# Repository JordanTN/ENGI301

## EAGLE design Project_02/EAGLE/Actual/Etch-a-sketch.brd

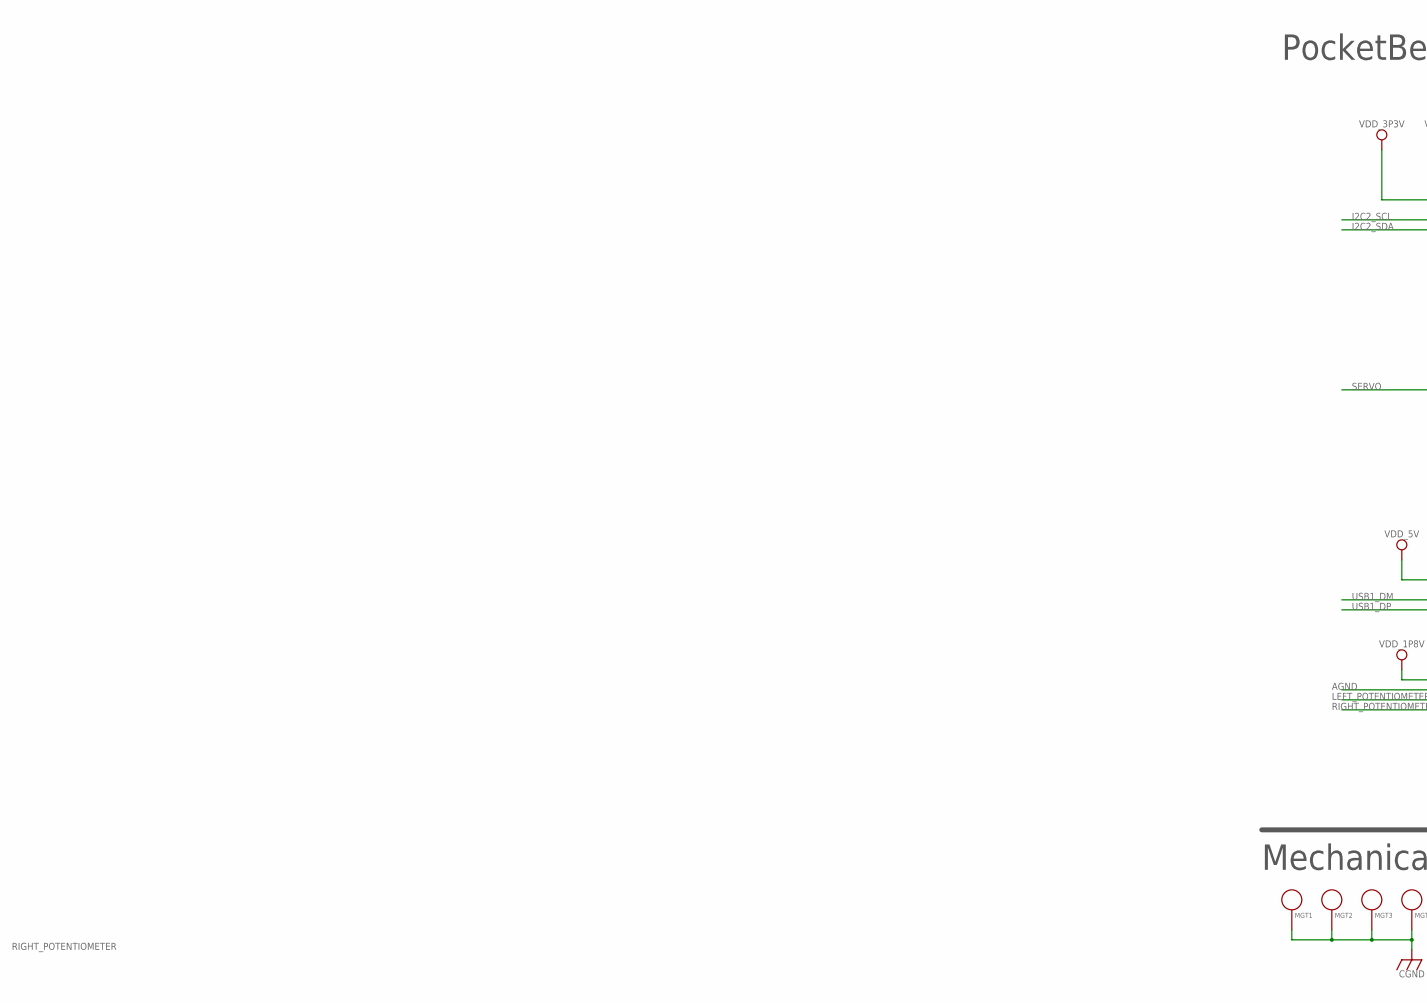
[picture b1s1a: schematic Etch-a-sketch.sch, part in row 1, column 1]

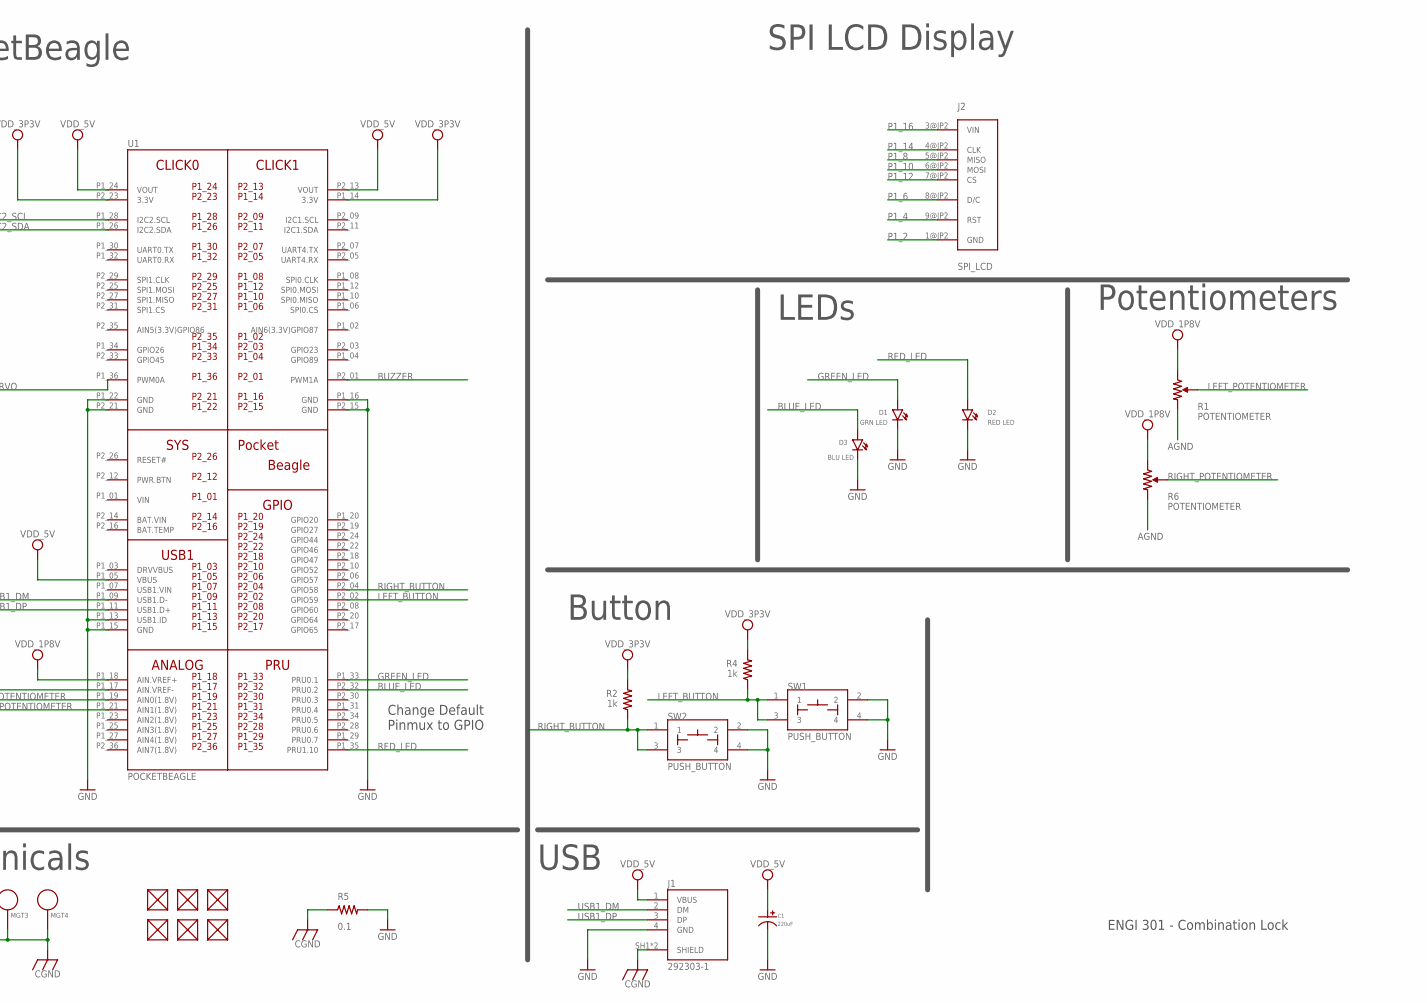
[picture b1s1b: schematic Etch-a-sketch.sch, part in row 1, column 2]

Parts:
C1: 220uF; CP10MM
D1, D3: GRN LED; EIA-STD
D2: RED LED; EIA-STD
FUD1, FUD2, FUD3, FUD4, FUD5, FUD6: FIDUCIAL; FIDUCIAL_40MIL
J1: 292303-1; TE_292303-1
J2: SPI_LCD; TFT_LCD_PCB
MGT1, MGT2, MGT3, MGT4: MOUNTING_HOLE
R1, R6: POTENTIOMETER; POT-PO90S
R2, R4: 1k; R0603
R5: 0.1; R0805
SW1, SW2: PUSH_BUTTON; BUTTON_12.5MM
U1: POCKETBEAGLE

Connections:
AGND: R1.CW, R6.CW, U1.P1_17 (AIN.VREF-)
AGND1: U1.P1_21 (AIN1(1.8V))
BAT.VIN: U1.P2_14 (BAT.VIN)
BUTTON1: U1.P2_04 (GPIO58)
BUZZER: U1.P2_01 (PWM1A)
CGND: J1.SH1 (SHIELD), J1.SH2 (SHIELD), MGT1.P$1, MGT2.P$1, MGT3.P$1, MGT4.P$1, R5.1
GND: C1.P$2, D1.CATHODE, D2.CATHODE, D3.CATHODE, J1.4 (GND), R5.2, SW1.2, SW1.4, SW2.2, SW2.4, U1.P1_13 (USB1.ID), U1.P1_15 (GND), U1.P1_16 (GND), U1.P1_22 (GND), U1.P2_15 (GND), U1.P2_21 (GND)
GREEN_LED: D1.ANODE, D3.ANODE, U1.P1_33 (PRU0.1)
GREEN_LED1: U1.P2_32 (PRU0.2)
I2C2_SCL: U1.P1_28 (I2C2.SCL)
I2C2_SDA: U1.P1_26 (I2C2.SDA)
LEFT_BUTTON: R2.1, R4.1, SW1.1, SW1.3, SW2.1, SW2.3, U1.P2_02 (GPIO59)
LEFT_POTENTIOMETER: R1.S, R6.S, U1.P1_19 (AIN0(1.8V))
RED_LED: D2.ANODE, U1.P1_35 (PRU1.10)
SERVO: U1.P1_36 (PWM0A)
USB1_DM: J1.2 (DM), U1.P1_09 (USB1.D-)
USB1_DP: J1.3 (DP), U1.P1_11 (USB1.D+)
VDD_1P8V: R1.CCW, R6.CCW, U1.P1_18 (AIN.VREF+)
VDD_3P3V: R2.2, R4.2, U1.P1_14 (3.3V), U1.P2_23 (3.3V)
VDD_5V: C1.P$1, J1.1 (VBUS), U1.P1_05 (VBUS), U1.P1_24 (VOUT), U1.P2_13 (VOUT)
VIN: U1.P1_01 (VIN)

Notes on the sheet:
LEDs
Potentiometers
SPI LCD Display
Button
PocketBeagle
ENGI 301 - Combination Lock
Mechanicals
Change Default Pinmux to GPIO
USB
RIGHT_BUTTON
RIGHT_POTENTIOMETER
BLUE_LED
BLU LED
P1_16
P1_14
P1_8
P1_10
P1_12
P1_6
P1_4
P1_2

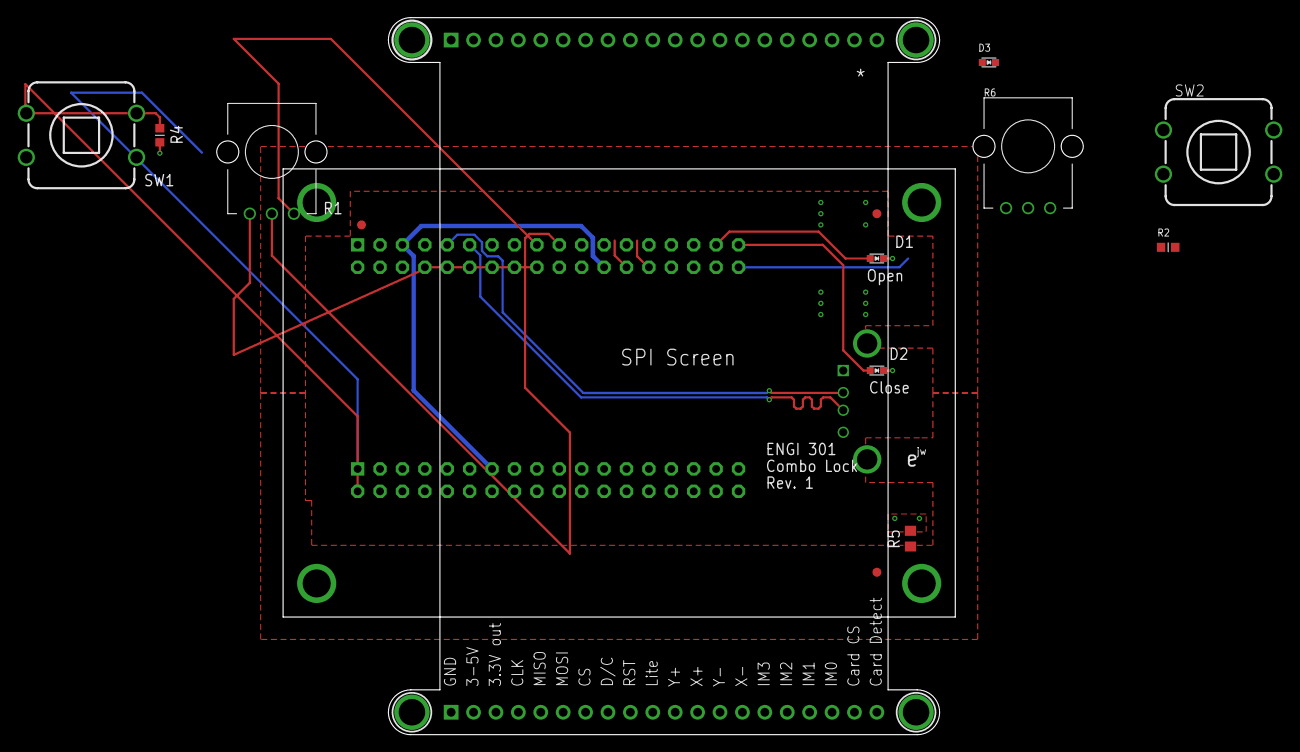
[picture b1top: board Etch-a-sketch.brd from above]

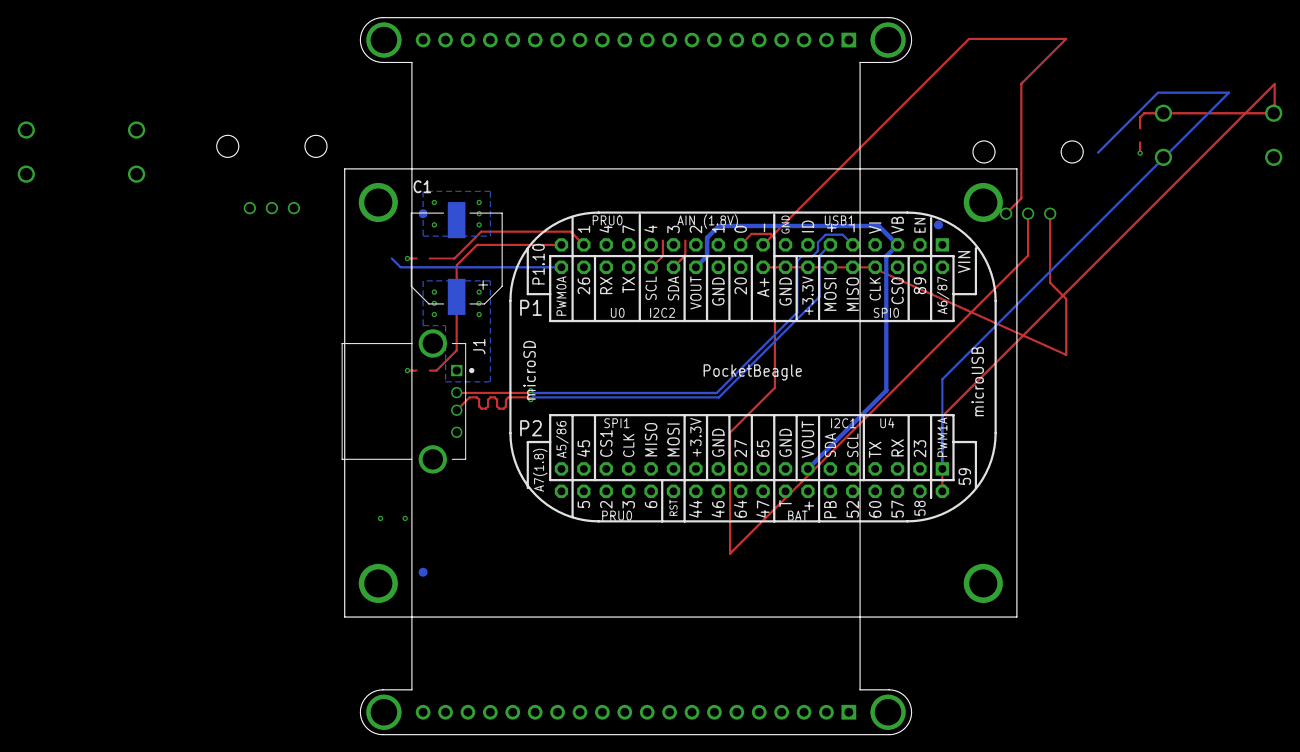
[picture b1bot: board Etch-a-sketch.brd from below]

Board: 4 copper layers, 24 parts (6 on the bottom side), 12 nets.

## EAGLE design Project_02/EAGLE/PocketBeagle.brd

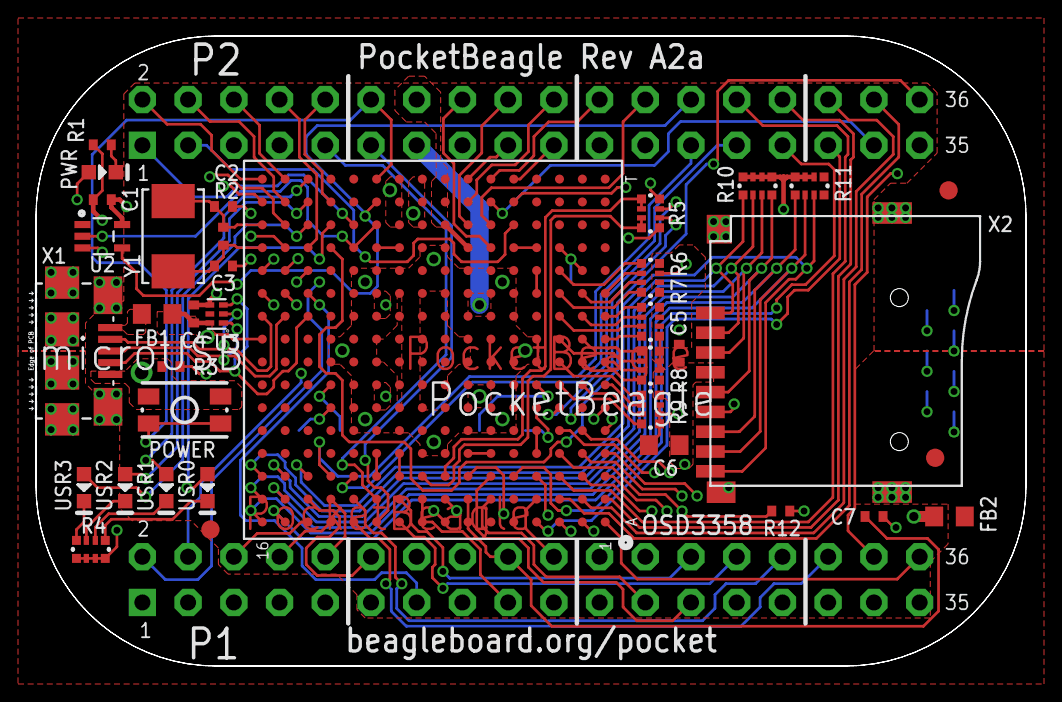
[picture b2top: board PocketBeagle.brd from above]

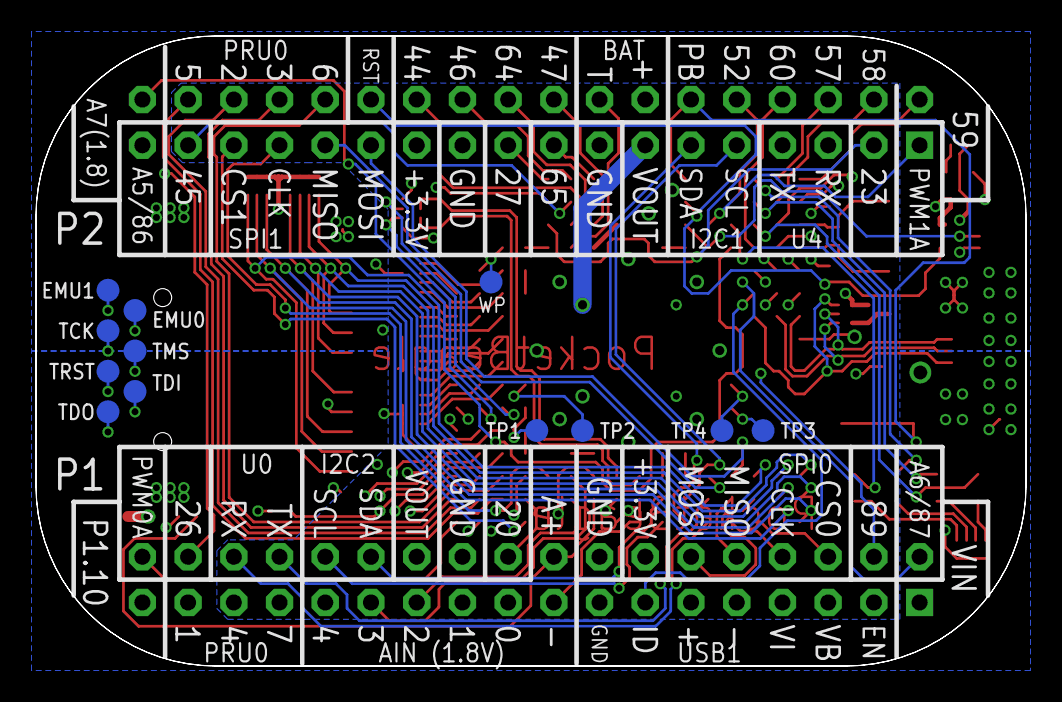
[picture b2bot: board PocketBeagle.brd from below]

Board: 4 copper layers, 55.0 x 35.0 mm, 50 parts (12 on the bottom side), 133 nets.

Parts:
C1, C5, C7: 0.1uF, 6.3V; 0402
C2, C3: 18pF, 50V; 0402
C4: .1uF, 6.3V; 0402
C6: 10uF, 10V; 0603
EMU0, EMU1: PTR1B1,27; B1,27
FB1, FB2: 0603
FUD1, FUD2, FUD3: FIDUCIAL; FIDUCIAL_40MIL
P1, P2: TH-2X18-(35MIL-DIA)-W/O-SILK
POWER: MINI_PUSHBUTTON
PWR: LTST-C191TBKT; 0603-LED
R1: 1k; 0402
R2: 1M, 1%; 0402
R3, R12: 10k; 0402
R4: 1k; RN0804
R5, R10, R11: 10k; RN0804
R6, R7, R8, R9: 100k; RN0804
TCK: PTR1B1,27; B1,27
TDI: PTR1B1,27; B1,27
TDO: PTR1B1,27; B1,27
TMS: PTR1B1,27; B1,27
TP1, TP2, TP3, TP4: PTR1B1,27; B1,27
TRST: PTR1B1,27; B1,27
U1: OSD3358-512M-BSM; OSD335X-BGA-256
U2: SN74LVC1G07DCK; SC70(TI-DCK)
U3: TPD4S012DRY; SON-6(TI)-DRY
USR0, USR1, USR2, USR3: LTST-C191TBKT; 0603-LED
WP: PTR1B1,27; B1,27
X1: 10118192-0001LF; 10118192-0001LF(MICRO-USB-B-AMPHENOL-FCI)
X2: MICROSD
Y1: 24 MHz; CRYSTAL_5X3.2MM

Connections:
3.3V: C5.1, C6.1, P1.14, P2.23, R6.7, R8.5, R9.4, R10.5, R10.6, R10.7, R10.8, R11.2, R11.3, R11.4, U1.F6, U1.F7, U1.G6, U1.G7, X2.4
(U1.A15)MMC0.D1: R11.6, U1.A15, X2.8
(U1.A16)MMC0.D0: R11.5, U1.A16, X2.7
(U1.B15)MMC0.CLK: R10.4, U1.B15, X2.5
(U1.B16)MMC0.CMD: R10.3, U1.B16, X2.3
(U1.C8)AIN5~1.8V: R5.1, R5.2, U1.C8
(U1.C9)AIN6~1.8V: R5.3, R5.4, U1.C9
(U1.C14)MMC0.CD: R11.7, U1.C14, X2.9
(U1.C15)MMC0.D3: R10.2, U1.C15, X2.2
(U1.C16)MMC0.D2: R10.1, U1.C16, X2.1
(U1.G1)LCD.D2.B5: R9.6, U1.G1
(U1.G2)LCD.D1.B4: R9.7, U1.G2
(U1.G3)LCD.D0.B3: R9.8, U1.G3
(U1.H1)LCD.D5.G2: R8.3, U1.H1
(U1.H2)LCD.D4.B7: R8.4, U1.H2
(U1.H3)LCD.D3.B6: R9.5, U1.H3
(U1.J1)LCD.D8.G5: R7.4, U1.J1
(U1.J2)LCD.D7.G4: R8.1, U1.J2
(U1.J3)LCD.D6.G3: R8.2, U1.J3
(U1.K1)LCD.D11.R3: R7.1, U1.K1
(U1.K2)LCD.D10.G7: R7.2, U1.K2
(U1.K3)LCD.D9.G6: R7.3, U1.K3
(U1.K14)USBC.ID: U1.K14, U3.3, X1.ID
(U1.K15)USBC.D+: U1.K15, U3.1, X1.D+
(U1.K16)USBC.D-: U1.K16, U3.2, X1.D-
(U1.L1)LCD.D14.R6: R6.2, U1.L1
(U1.L2)LCD.D13.R5: R6.3, U1.L2
(U1.L3)LCD.D12.R4: R6.4, U1.L3
(U1.M2)EEPROM.WP: U1.M2, U1.N3, WP.TP
(U1.M3)LCD.D15.R7: R6.1, U1.M3
(U1.P13)USR0: U1.P13, USR0.A
(U1.P14)USR3: U1.P14, USR3.A
(U1.R14)USR2: U1.R14, USR2.A
(U1.T14)USR1: U1.T14, USR1.A
AIN0(1.8V): P1.19, U1.A8
AIN1(1.8V): P1.21, U1.B8
AIN2(1.8V): P1.23, U1.B6
AIN3(1.8V): P1.25, U1.C6
AIN4(1.8V): P1.27, U1.C7
AIN5(3.3V): P2.35, R5.7, U1.F3
AIN6/GPIO87: P1.2, R5.6, U1.F2
AIN7(1.8V): P2.36, U1.N13
AIN.VREF+: C7.1, P1.18, U1.A7, U1.B7
AIN.VREF-: C7.2, P1.17, U1.A9, U1.B9
BAT.TEMP: P2.16, U1.N6
BAT.VIN: P2.14, U1.N7, U1.P8, U1.R8, U1.T8
CGND: FB2.1, X1.CGND1, X1.CGND2, X1.CGND3, X1.CGND4, X1.CGND5, X1.CGND6, X2.G1, X2.G2, X2.G3, X2.G4
GND: C1.2, C4.2, C5.2, C6.2, FB2.2, P1.15, P1.16, P1.22, P2.15, P2.21, POWER.1, POWER.2, R1.1, R3.1, R4.5, R4.6, R4.7, R4.8, R5.5, R5.8, R6.5, R6.6, R6.8, R7.5, R7.6, R7.7, R7.8, R8.6, R8.7, R8.8, R9.1, R9.2, R9.3, R12.1, U1.D8, U1.D9, U1.E5, U1.E6, U1.E7, U1.E8, U1.E9, U1.E10, U1.E11, U1.E12, U1.F5, U1.F12, U1.G5, U1.G12, U1.H4, U1.H5, U1.H12, U1.H13, U1.J4, U1.J5, U1.J12, U1.J13, U1.K5, U1.K12, U1.L5, U1.L12, U1.M5, U1.M6, U1.M7, U1.M8, U1.M9, U1.M10, U1.M11, U1.M12, U1.N8, U1.N9, U2.3, U3.4, X1.GND, X2.6
GPIO20: P1.20, U1.B4
GPIO23: P2.3, U1.P5
GPIO26: P1.34, U1.R5
GPIO27: P2.19, U1.T5
GPIO44: P2.24, U1.P6
GPIO45: P2.33, U1.R6
GPIO46: P2.22, U1.T6
GPIO47: P2.18, U1.P7
GPIO52: P2.10, U1.R13
GPIO57: P2.6, U1.T15
GPIO58: P2.4, U1.R15
GPIO59: P2.2, U1.T16
GPIO60: P2.8, U1.N14
GPIO64: P2.20, U1.R7
GPIO65: P2.17, U1.T7
GPIO89: P1.4, U1.E1
I2C1.SCL: P2.9, U1.B11
I2C1.SDA: P2.11, U1.A11
I2C2.SCL: P1.28, U1.A10
I2C2.SDA: P1.26, U1.B10
JTAG_EMU0: EMU0.TP, U1.E2
JTAG_EMU1: EMU1.TP, U1.E3
JTAG_TCK: TCK.TP, U1.D1
JTAG_TDI: TDI.TP, U1.C1
JTAG_TDO: TDO.TP, U1.C2
JTAG_TMS: TMS.TP, U1.D2
JTAG_TRST#: R12.2, TRST.TP, U1.D3
unnamed: R4.3, USR2.K
unnamed: R4.4, USR3.K
unnamed: PWR.K, R1.2
unnamed: R4.2, USR1.K
unnamed: R4.1, USR0.K
unnamed: TP1.TP, U1.F4
unnamed: TP2.TP, U1.G4
unnamed: TP3.TP, U1.F13
unnamed: TP4.TP, U1.G13
unnamed: U1.D6, U1.D7
unnamed: R3.2, U1.M16
unnamed: U1.N4, U1.N5
unnamed: U1.L4, U1.M4
unnamed: U1.D4, U1.E4
unnamed: U1.N10, U1.N11
unnamed: U1.C11, U1.D11
unnamed: U1.C10, U1.D10
OSC.GND: C2.1, C3.1, U1.N15
OSC.IN: C2.2, R2.2, U1.P16, Y1.2
OSC.OUT: C3.2, R2.1, U1.N16, Y1.1
PMIC_PGOOD: U1.N12, U1.P11, U2.2
PRU0.1: P1.33, U1.A2
PRU0.2: P2.32, U1.B2
PRU0.3: P2.30, U1.B1
PRU0.4: P1.31, U1.A3
PRU0.5: P2.34, U1.B3
PRU0.6: P2.28, U1.C3
PRU0.7: P1.29, U1.C4
PRU1.10: P1.35, U1.F1
PWM0A: P1.36, U1.A1
PWM1A: P2.1, U1.P12
PWR.BTN: P2.12, POWER.3, POWER.4, U1.T11
RESET#: P2.26, U1.R11, U2.4
SPI0.CLK: P1.8, U1.A13
SPI0.CS: P1.6, U1.A14
SPI0.MISO: P1.10, U1.B13
SPI0.MOSI: P1.12, U1.B14
SPI1.CLK: P2.29, U1.C5
SPI1.CS: P2.31, U1.A4
SPI1.MISO: P2.27, U1.C12
SPI1.MOSI: P2.25, U1.C13
UART0.RX: P1.32, U1.A12
UART0.TX: P1.30, U1.B12
UART4.RX: P2.5, U1.P15
UART4.TX: P2.7, U1.R16
USB1.D+: P1.11, U1.L15
USB1.D-: P1.9, U1.L16
USB1.DRVVBUS: P1.3, U1.M14
USB1.ID: P1.13, U1.L14
USB1.VBUS: P1.5, U1.M15
VBUS.RAW: FB1.1, X1.VBUS
VDD_1V8: U1.F10, U1.G10, U1.H10, U1.H11, U1.J10, U1.J11, U1.K10, U1.L10
VDD_3V3A: U1.F8, U1.F9, U1.G8, U1.G9, U1.H7, U1.H8, U1.H9, U1.J7, U1.J8, U1.J9, U1.K8, U1.K9, U1.L8, U1.L9
VDD_3V3AUX: PWR.A, U1.F11, U1.G11
VDD_RTC: C1.1, U1.K11, U1.L11, U2.5
VIN: P1.1, U1.P10, U1.R10, U1.T10
VIN.USB: C4.1, FB1.2, P1.7, U1.J16, U1.P9, U1.R9, U1.T9, U3.6
VOUT: P1.24, P2.13, U1.K6, U1.K7, U1.L6, U1.L7

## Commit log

2022-09-19 hw4 question1 added
2022-09-19 blink USR3 at 5 Hz
2022-10-04 Create proposal
2022-12-03 1st update
2022-12-05 README
2022-12-06 downloading files
2022-12-08 12-7
2022-12-09 12 9
2022-12-09 etch the sketch
